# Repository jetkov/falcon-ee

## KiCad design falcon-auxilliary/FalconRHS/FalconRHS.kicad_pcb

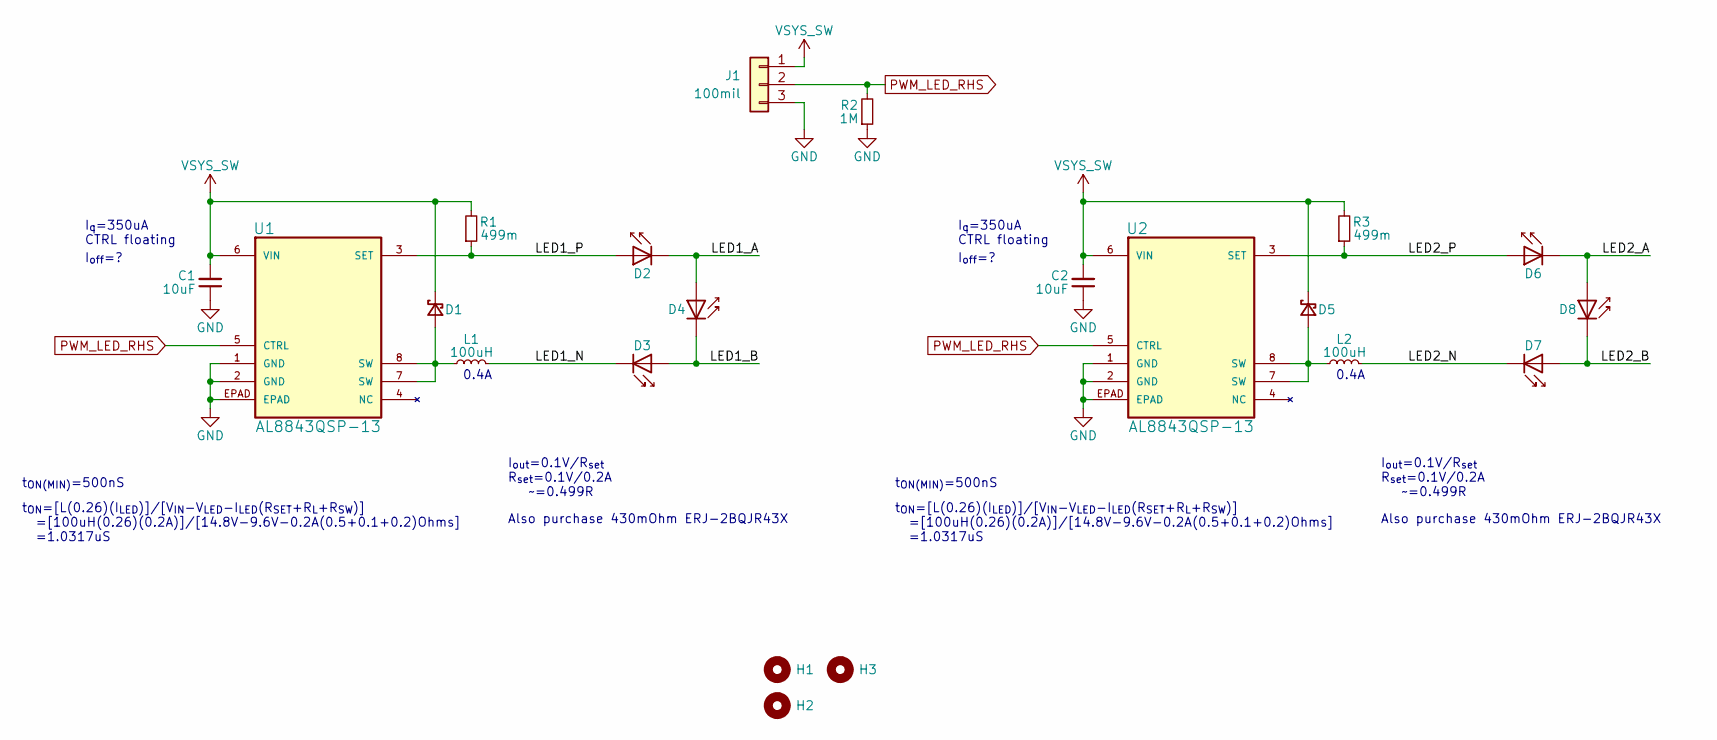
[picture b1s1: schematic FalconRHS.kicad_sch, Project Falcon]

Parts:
C1, C2: 10uF; C_1210_3225Metric; Tolerance 10%; Voltage 50V; Part Number CGA6P3X7S1H106K250AB
D1, D5: 500mA; SC-76-SOD-323_USC_TSB; Part Number CUS551V30,H3F
D2, D3, D4, D6, D7, D8: XQA LED 1616 SMD; XQ-A-LED_Large; Voltage 3.4Vf; Part Number XQAAPA-02-0000-000000Y01
H1, H2, H3: MountingHole; MountingHole_2.7mm_M2.5_Clearanced
J1: 100mil; PinHeader_1x03_P2.54mm_Vertical
L1, L2: 100uH; L_Taiyo-Yuden_NR-60xx_HandSoldering; Tolerance 20%; Part Number NR6028T101M
R1, R3: 499m; R_0402_1005Metric; Tolerance 1%; Part Number RL0402FR-070R499L
R2: 1M; R_0402_1005Metric; Tolerance 1%; Part Number RMCF0402FT1M00
U1, U2: AL8843QSP-13; 8-SOIC_SO-8EP_DIO; Part Number AL8843QSP-13

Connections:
/LED1_A: D2.1 (K), D4.2 (A)
/LED1_B: D3.2 (A), D4.1 (K)
/LED1_N: D3.1 (K), L1.2
/LED1_P: D2.2 (A), R1.1, U1.3 (SET)
/LED2_A: D6.1 (K), D8.2 (A)
/LED2_B: D7.2 (A), D8.1 (K)
/LED2_N: D7.1 (K), L2.2
/LED2_P: D6.2 (A), R3.1, U2.3 (SET)
GND: C1.1, C2.1, J1.3, R2.1, U1.1 (GND), U1.2 (GND), U1.EPAD, U2.1 (GND), U2.2 (GND), U2.EPAD
unnamed: D1.2 (A), L1.1, U1.7 (SW), U1.8 (SW)
unnamed: D5.2 (A), L2.1, U2.7 (SW), U2.8 (SW)
PWM_LED_RHS: J1.2, R2.2, U1.5 (CTRL), U2.5 (CTRL)
VSYS_SW: C1.2, C2.2, D1.1 (K), D5.1 (K), J1.1, R1.2, R3.2, U1.6 (VIN), U2.6 (VIN)

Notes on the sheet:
Also purchase 430mOhm ERJ-2BQJR43X
I_{off}=?
t_{ON(MIN)}=500nS
I_{q}=350uA CTRL floating
t_{ON}=[L(0.26)(I_{LED})]/[V_{IN}-V_{LED}-I_{LED}(R_{SET}+R_{L}+R_{SW})] =[100uH(0.26)(0.2A)]/[14.8V-9.6V-0.2A(0.5+0.1+0.2)Ohms] =1.0317uS
I_{out}=0.1V/R_{set} R_{set}=0.1V/0.2A ~=0.499R
0.4A

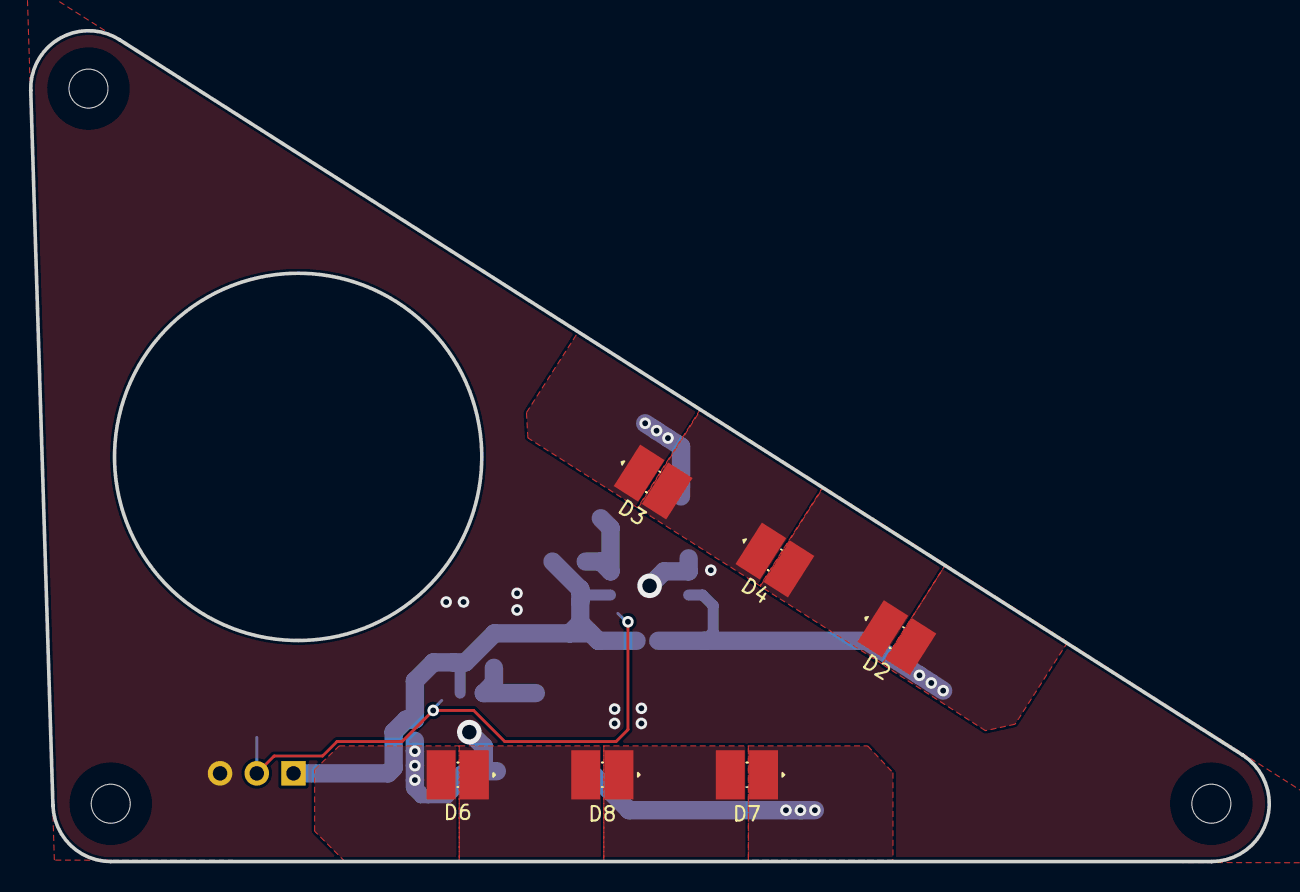
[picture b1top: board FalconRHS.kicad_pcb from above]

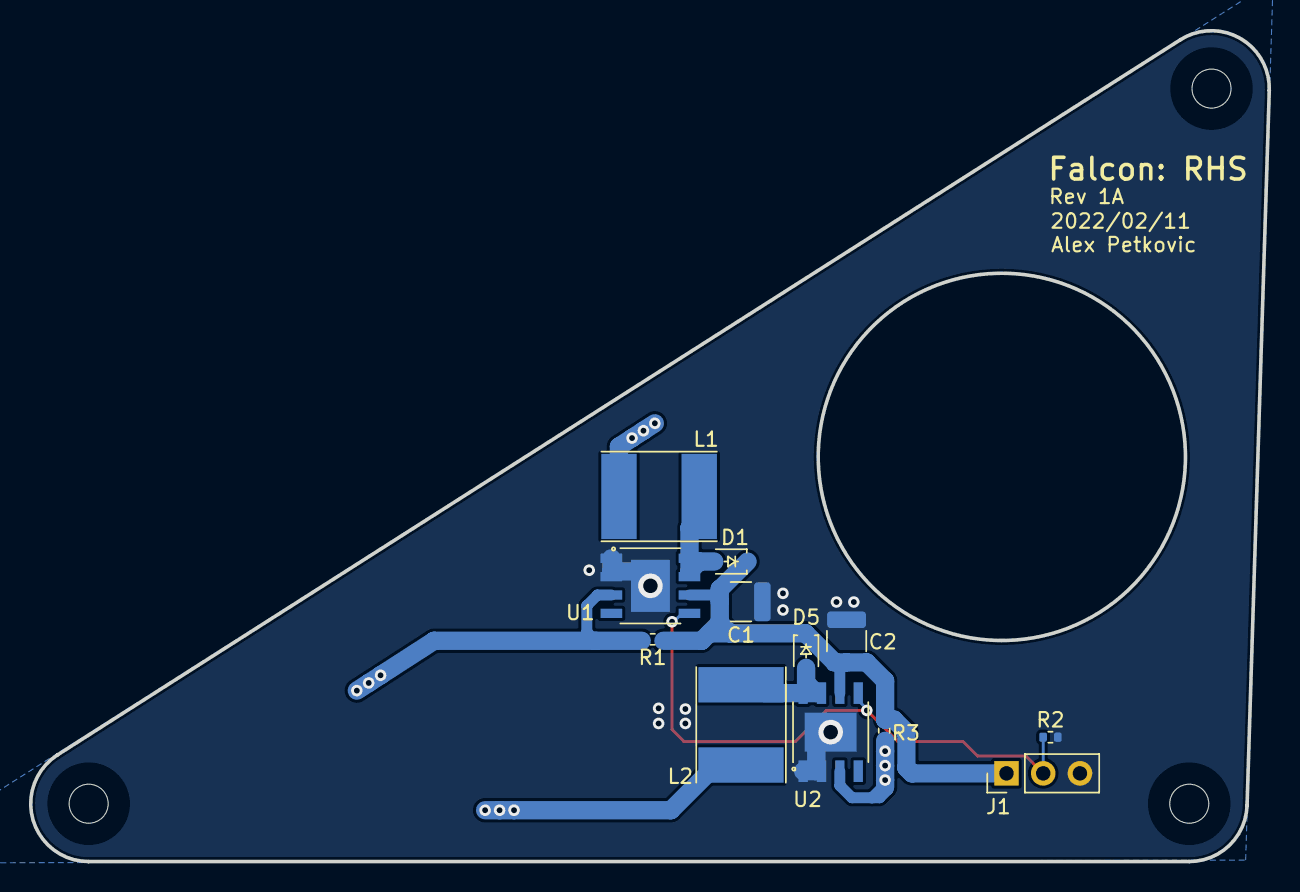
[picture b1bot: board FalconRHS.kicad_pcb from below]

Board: 2 copper layers, 85.7 x 57.5 mm, 21 parts (12 on the bottom side), 13 nets.

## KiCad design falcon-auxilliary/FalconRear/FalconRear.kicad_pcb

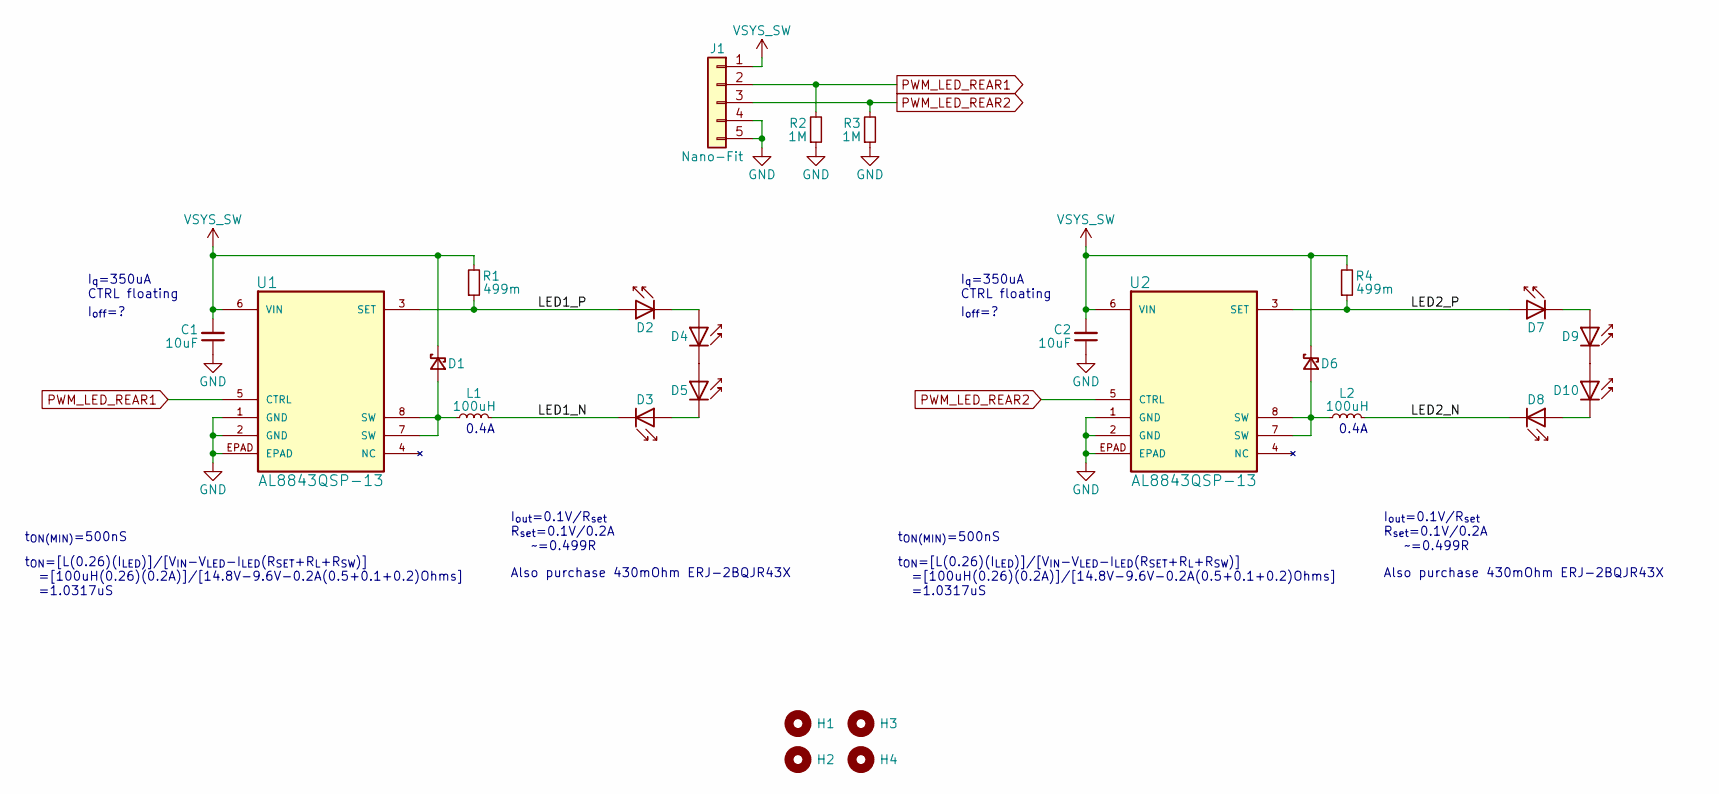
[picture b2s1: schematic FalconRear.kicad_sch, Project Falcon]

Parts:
C1, C2: 10uF; C_1210_3225Metric; Tolerance 10%; Voltage 50V; Part Number CGA6P3X7S1H106K250AB
D1, D6: 500mA; SC-76-SOD-323_USC_TSB; Part Number CUS551V30,H3F
D2, D3, D4, D5, D7, D8, D9, D10: XQA LED 1616 SMD; XQ-A-LED_Large; Voltage 2,2Vf; Part Number XQARED-02-0000-000000W01
H1, H2, H3, H4: MountingHole; MountingHole_2.7mm_M2.5_Clearanced
J1: Nano-Fit; Molex_Nano-Fit_105313-xx05_1x05_P2.50mm_Horizontal; Part Number 1053091105
L1, L2: 100uH; L_Taiyo-Yuden_NR-60xx_HandSoldering; Tolerance 20%; Part Number NR6028T101M
R1, R4: 499m; R_0402_1005Metric; Tolerance 1%; Part Number RL0402FR-070R499L
R2, R3: 1M; R_0402_1005Metric; Tolerance 1%; Part Number RMCF0402FT1M00
U1, U2: AL8843QSP-13; 8-SOIC_SO-8EP_DIO; Part Number AL8843QSP-13

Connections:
/LED1_N: D3.1 (K), L1.2
/LED1_P: D2.2 (A), R1.1, U1.3 (SET)
/LED2_N: D8.1 (K), L2.2
/LED2_P: D7.2 (A), R4.1, U2.3 (SET)
GND: C1.1, C2.1, J1.4, J1.5, R2.1, R3.1, U1.1 (GND), U1.2 (GND), U1.EPAD, U2.1 (GND), U2.2 (GND), U2.EPAD
unnamed: D1.2 (A), L1.1, U1.7 (SW), U1.8 (SW)
unnamed: D2.1 (K), D4.2 (A)
unnamed: D3.2 (A), D5.1 (K)
unnamed: D4.1 (K), D5.2 (A)
unnamed: D6.2 (A), L2.1, U2.7 (SW), U2.8 (SW)
unnamed: D7.1 (K), D9.2 (A)
unnamed: D8.2 (A), D10.1 (K)
unnamed: D9.1 (K), D10.2 (A)
PWM_LED_REAR1: J1.2, R2.2, U1.5 (CTRL)
PWM_LED_REAR2: J1.3, R3.2, U2.5 (CTRL)
VSYS_SW: C1.2, C2.2, D1.1 (K), D6.1 (K), J1.1, R1.2, R4.2, U1.6 (VIN), U2.6 (VIN)

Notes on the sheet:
Also purchase 430mOhm ERJ-2BQJR43X
I_{off}=?
t_{ON(MIN)}=500nS
I_{q}=350uA CTRL floating
t_{ON}=[L(0.26)(I_{LED})]/[V_{IN}-V_{LED}-I_{LED}(R_{SET}+R_{L}+R_{SW})] =[100uH(0.26)(0.2A)]/[14.8V-9.6V-0.2A(0.5+0.1+0.2)Ohms] =1.0317uS
I_{out}=0.1V/R_{set} R_{set}=0.1V/0.2A ~=0.499R
0.4A

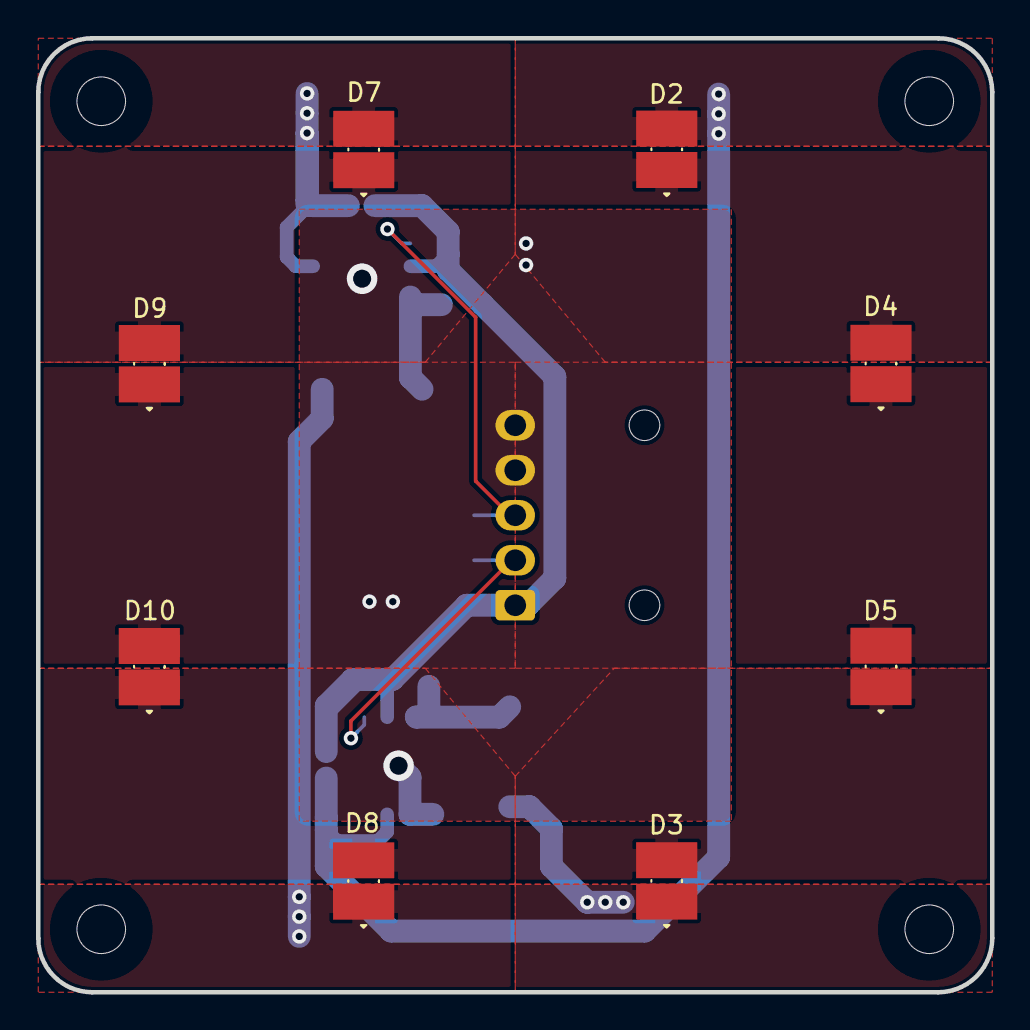
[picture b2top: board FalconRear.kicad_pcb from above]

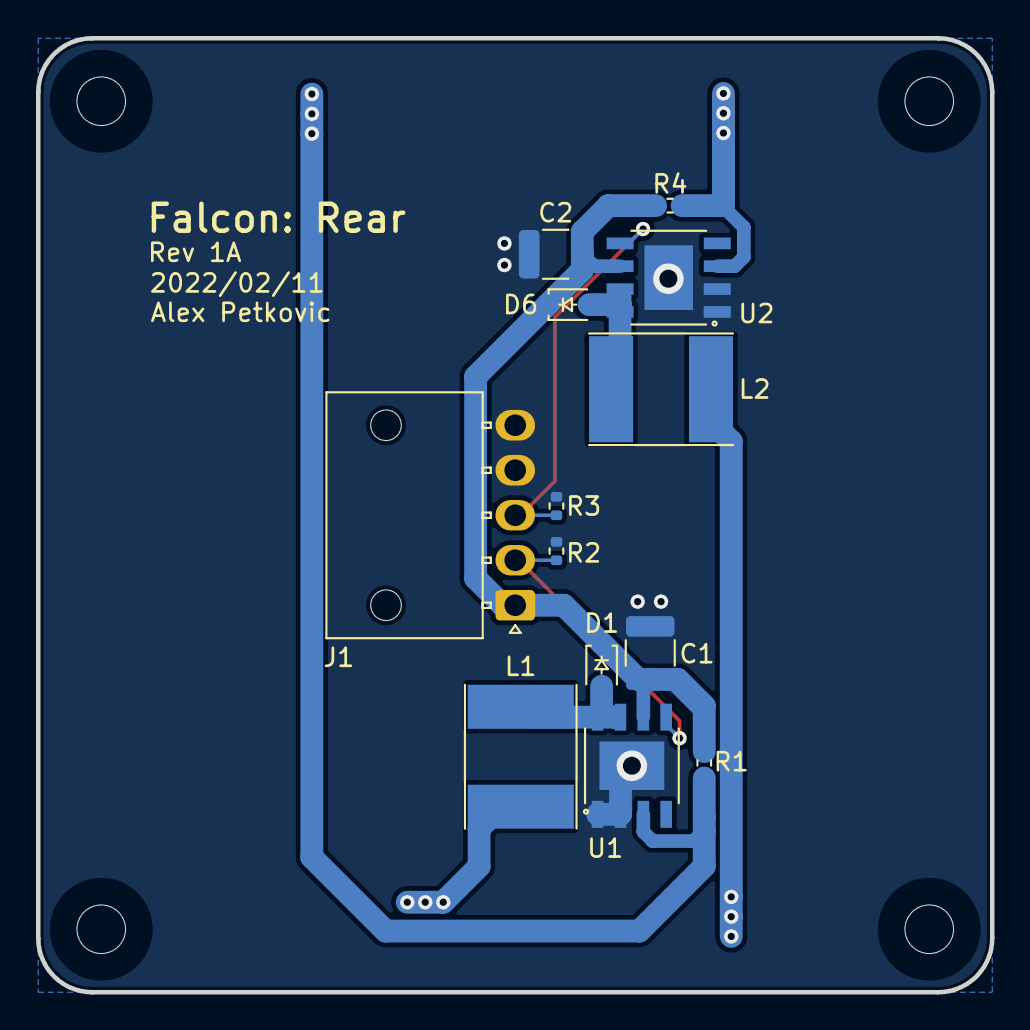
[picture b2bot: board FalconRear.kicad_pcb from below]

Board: 2 copper layers, 53.0 x 53.0 mm, 25 parts (13 on the bottom side), 16 nets.

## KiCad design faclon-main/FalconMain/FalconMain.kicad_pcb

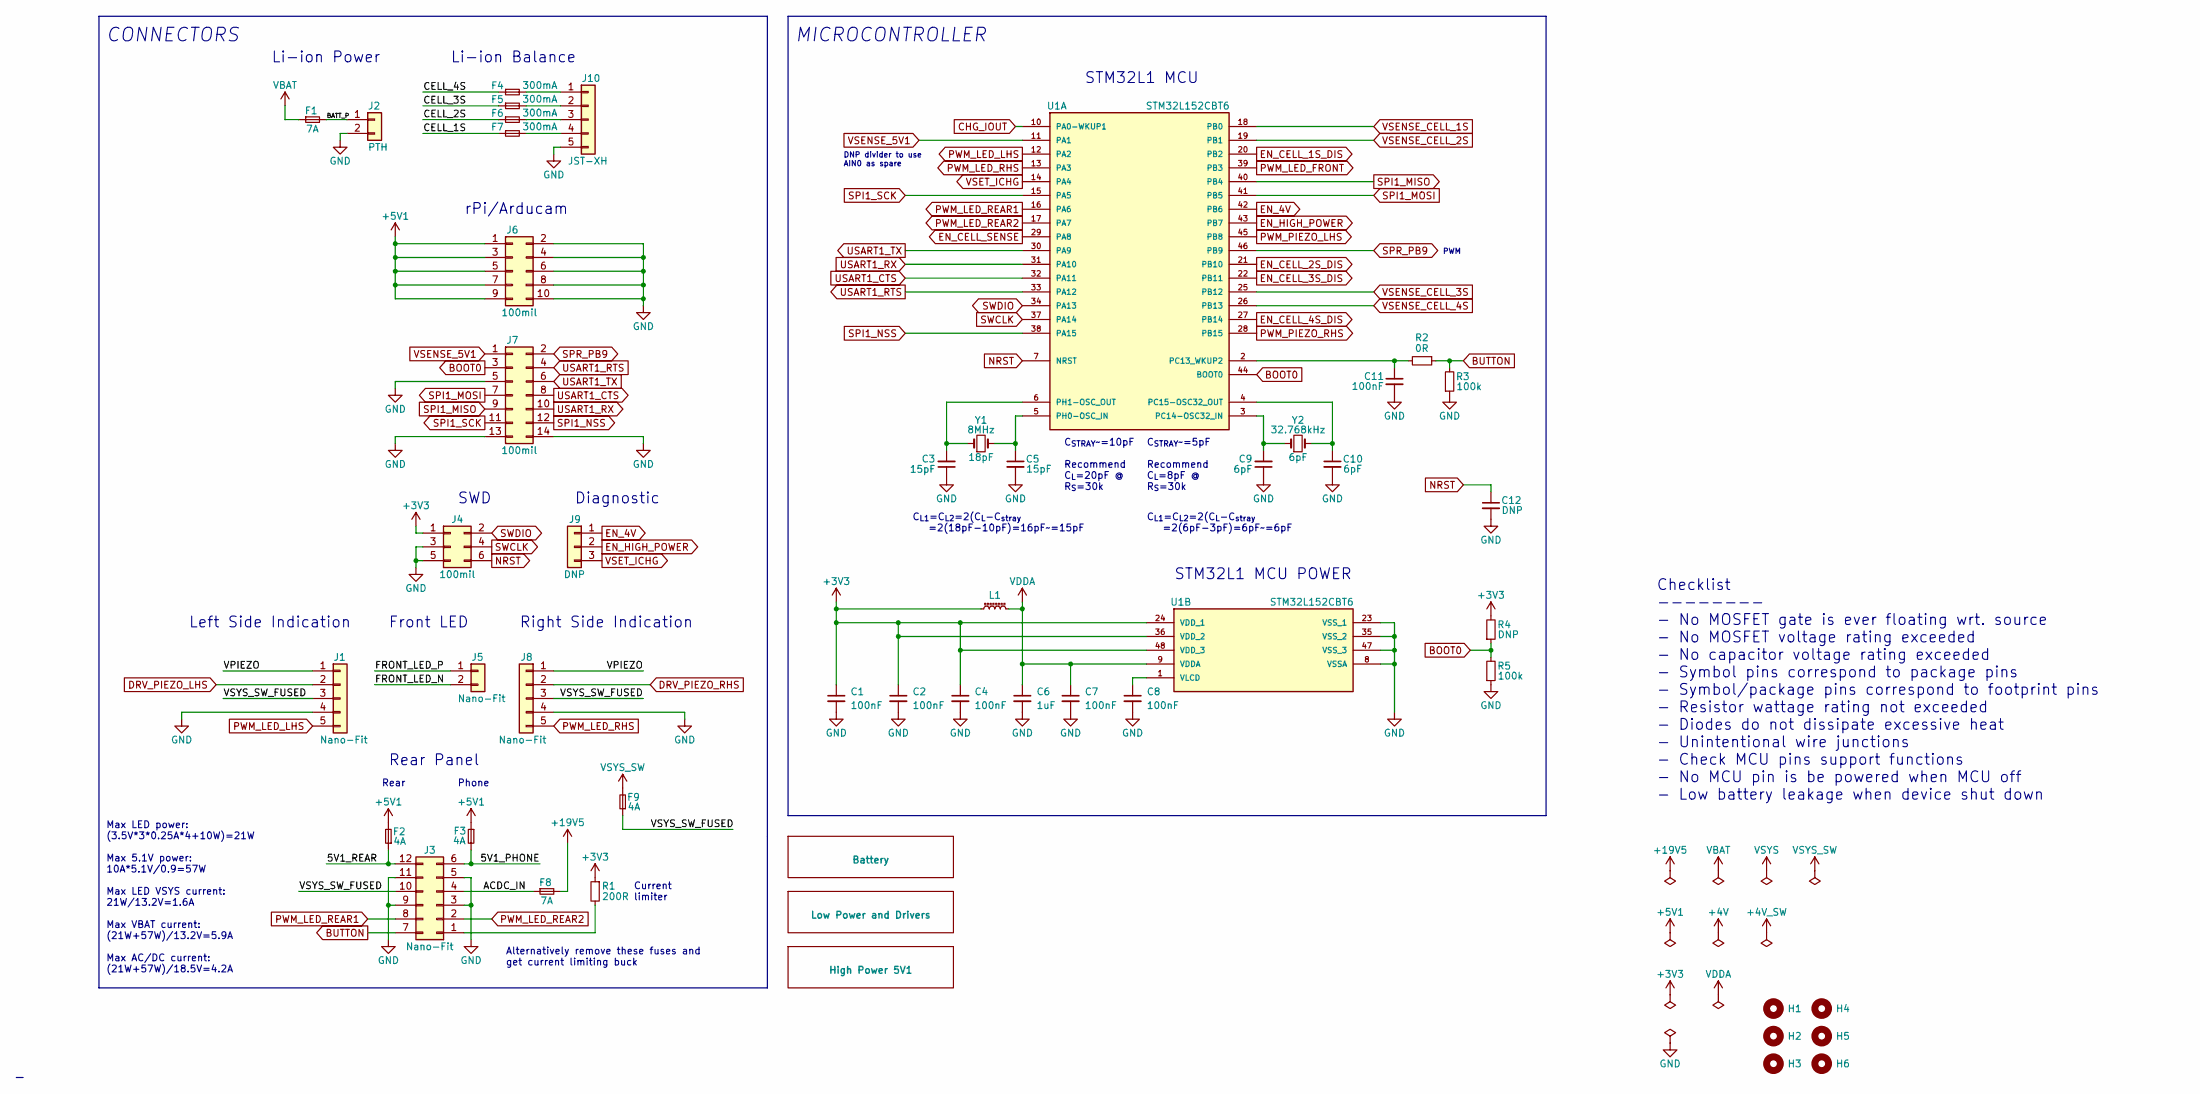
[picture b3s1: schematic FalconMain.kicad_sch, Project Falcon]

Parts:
C1, C2, C4, C7, C8, C11: 100nF; C_0402_1005Metric; Tolerance 10%; Voltage 25V; Part Number GRM155R71E104KE14D
C3, C5: 15pF; C_0402_1005Metric; Tolerance 5%; Voltage 50V; Part Number 885012005056
C6: 1uF; C_0603_1608Metric; Tolerance 10%; Voltage 25V; Part Number CGA3E1X7R1E105K080AC
C9, C10: 6pF; C_0402_1005Metric; Tolerance 0.5pF; Voltage 50V; Part Number CGA2B2C0G1H060D050BA
C12: DNP; C_0402_1005Metric; Tolerance 10%; Voltage 50V; Part Number 885012205061
F1, F8: 7A; R_0603_1608Metric; Voltage 32V; Part Number 0686F7000-01
F2, F3, F9: 4A; R_0402_1005Metric; Voltage 32V; Part Number 3414.0123.26
F4, F5, F6, F7: 300mA; R_0603_1608Metric; Voltage 32V; Part Number C2Q 300
H1, H2, H3, H4, H5, H6: MountingHole; MountingHole_2.7mm_M2.5_Clearanced
J1, J8: Nano-Fit; Molex_Nano-Fit_105309-xx05_1x05_P2.50mm_Vertical; Part Number 1053091105
J2: PTH; Conn_Batt_Wire_10AWG
J3: Nano-Fit; Molex_Nano-Fit_105310-xx12_2x06_P2.50mm_Vertical; Part Number 1053101112
J4: 100mil; PinHeader_2x03_P2.54mm_Vertical; Part Number PREC003DFAN-RC
J5: Nano-Fit; Molex_Nano-Fit_105309-xx02_1x02_P2.50mm_Vertical; Part Number 1053091102
J6: 100mil; PinHeader_2x05_P2.54mm_Vertical
J7: 100mil; PinHeader_2x07_P2.54mm_Vertical
J9: DNP; PinHeader_1x03_P2.54mm_Vertical; Part Number PREC040SAAN-RC
J10: JST-XH; JST_XH_B5B-XH-AM_1x05_P2.50mm_Vertical; Part Number B5B-XH-AM(LF)(SN)
L1: 600 Ohms @ 100 MHz; L_0402_1005Metric; Part Number BLM15AX601SN1D
R1: 200R; R_0603_1608Metric; Tolerance 5%; Part Number RMCF0603JT200R
R2: 0R; R_0402_1005Metric; Tolerance Jumper; Part Number RMCF0402ZT0R00
R3, R5: 100k; R_0402_1005Metric; Tolerance 1%; Part Number RC0402FR-13100KL
R4: DNP; R_0402_1005Metric; Tolerance 1%; Part Number RC0402FR-13100KL
U1: STM32L152CBT6; 48-LQFP_ LQFP48_STM; Part Number STM32L152CBT6
Y1: 8MHz; Crystal_SMD_HC49_WURTH; Tolerance 30ppm; Part Number 830050510
Y2: 32.768kHz; Crystal_DS26_D2.0mm_L6.0mm_Horizontal; Tolerance 20ppm; Part Number 830014219B

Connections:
+3V3: C1.1, C2.1, C4.1, J4.1, L1.1, R1.1, R4.2, U1.24 (VDD_1), U1.36 (VDD_2), U1.48 (VDD_3); also elsewhere on the board
+5V1: F2.2, F3.1, J6.1, J6.3, J6.5, J6.7, J6.9; also elsewhere on the board
+19V5: F8.2; also elsewhere on the board
/5V1_PHONE: F3.2, J3.6
/5V1_REAR: F2.1, J3.12
/ACDC_IN: F8.1, J3.4
/BATT_P: F1.2, J2.1
/CELL_1S: F7.1
/CELL_2S: F6.1
/CELL_3S: F5.1
/CELL_4S: F4.1
/FRONT_LED_N: J5.2
/FRONT_LED_P: J5.1
/VPIEZO: J1.1, J8.1
/VSYS_SW_FUSED: F9.1, J1.3, J3.10, J8.3
BOOT0: J7.3, R4.1, R5.2, U1.44 (BOOT0)
BUTTON: J3.7, R2.1, R3.2
CHG_IOUT: U1.10 (PA0-WKUP1); also elsewhere on the board
DRV_PIEZO_LHS: J1.2; also elsewhere on the board
DRV_PIEZO_RHS: J8.2; also elsewhere on the board
EN_4V: J9.1, U1.42 (PB6); also elsewhere on the board
EN_CELL_1S_DIS: U1.20 (PB2); also elsewhere on the board
EN_CELL_2S_DIS: U1.21 (PB10); also elsewhere on the board
EN_CELL_3S_DIS: U1.22 (PB11); also elsewhere on the board
EN_CELL_4S_DIS: U1.27 (PB14); also elsewhere on the board
EN_CELL_SENSE: U1.29 (PA8); also elsewhere on the board
EN_HIGH_POWER: J9.2, U1.43 (PB7); also elsewhere on the board
GND: C1.2, C2.2, C3.1, C4.2, C5.2, C6.2, C7.2, C8.2, C9.1, C10.2, C11.2, C12.2, J1.4, J2.2, J3.3, J3.5, J3.9, J3.11, J4.3, J4.5, J6.2, J6.4, J6.6, J6.8, J6.10, J7.5, J7.13, J7.14, J8.4, J10.5, R3.1, R5.1, U1.8 (VSSA), U1.23 (VSS_1), U1.35 (VSS_2), U1.47 (VSS_3); also elsewhere on the board
NRST: C12.1, J4.6, U1.7 (NRST)
unnamed: C3.2, U1.6 (PH1-OSC_OUT), Y1.1
unnamed: C5.1, U1.5 (PH0-OSC_IN), Y1.2
unnamed: C8.1, U1.1 (VLCD)
unnamed: C9.2, U1.3 (PC14-OSC32_IN), Y2.1
unnamed: C10.1, U1.4 (PC15-OSC32_OUT), Y2.2
unnamed: C11.1, R2.2, U1.2 (PC13_WKUP2)
unnamed: F4.2, J10.1
unnamed: F5.2, J10.2
unnamed: F6.2, J10.3
unnamed: F7.2, J10.4
unnamed: J3.1, R1.2
PWM_LED_FRONT: U1.39 (PB3); also elsewhere on the board
PWM_LED_LHS: J1.5, U1.12 (PA2)
PWM_LED_REAR1: J3.8, U1.16 (PA6)
PWM_LED_REAR2: J3.2, U1.17 (PA7)
PWM_LED_RHS: J8.5, U1.13 (PA3)
PWM_PIEZO_LHS: U1.45 (PB8); also elsewhere on the board
PWM_PIEZO_RHS: U1.28 (PB15); also elsewhere on the board
SPI1_MISO: J7.9, U1.40 (PB4)
SPI1_MOSI: J7.7, U1.41 (PB5)
SPI1_NSS: J7.12, U1.38 (PA15)
SPI1_SCK: J7.11, U1.15 (PA5)
SPR_PB9: J7.2, U1.46 (PB9)
SWCLK: J4.4, U1.37 (PA14)
SWDIO: J4.2, U1.34 (PA13)
USART1_CTS: J7.8, U1.32 (PA11)
USART1_RTS: J7.4, U1.33 (PA12)
USART1_RX: J7.10, U1.31 (PA10)
USART1_TX: J7.6, U1.30 (PA9)
VBAT: F1.1; also elsewhere on the board
VDDA: C6.1, C7.1, L1.2, U1.9 (VDDA)
VSENSE_5V1: J7.1, U1.11 (PA1); also elsewhere on the board
VSENSE_CELL_1S: U1.18 (PB0); also elsewhere on the board
VSENSE_CELL_2S: U1.19 (PB1); also elsewhere on the board
VSENSE_CELL_3S: U1.25 (PB12); also elsewhere on the board
VSENSE_CELL_4S: U1.26 (PB13); also elsewhere on the board
VSET_ICHG: J9.3, U1.14 (PA4); also elsewhere on the board
VSYS_SW: F9.2; also elsewhere on the board

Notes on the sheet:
Left Side Indication
STM32L1 MCU
rPi/Arducam
Right Side Indication
Current limiter
CONNECTORS
Rear
Rear Panel
Phone
Alternatively remove these fuses and get current limiting buck
PWM
STM32L1 MCU POWER
MICROCONTROLLER
SWD
C_{L1}=C_{L2}=2(C_{L}-C_{stray} =2(18pF-10pF)=16pF~=15pF
Li-ion Power
C_{L1}=C_{L2}=2(C_{L}-C_{stray} =2(6pF-3pF)=6pF~=6pF
DNP divider to use AIN0 as spare
Max LED power: (3.5V*3*0.25A*4+10W)=21W Max 5.1V power: 10A*5.1V/0.9=57W Max LED VSYS current: 21W/13.2V=1.6A Max VBAT current: (21W+57W)/13.2V=5.9A Max AC/DC current: (21W+57W)/18.5V=4.2A
Diagnostic
C_{STRAY}~=5pF Recommend C_{L}=8pF @ R_{S}=30k
Checklist -------- - No MOSFET gate is ever floating wrt. source - No MOSFET voltage rating exceeded - No capacitor voltage rating exceeded - Symbol pins correspond to package pins - Symbol/package pins correspond to footprint pins - Resistor wattage rating not exceeded - Diodes do not dissipate ex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
C_{STRAY}~=10pF Recommend C_{L}=20pF @ R_{S}=30k
Front LED
Li-ion Balance

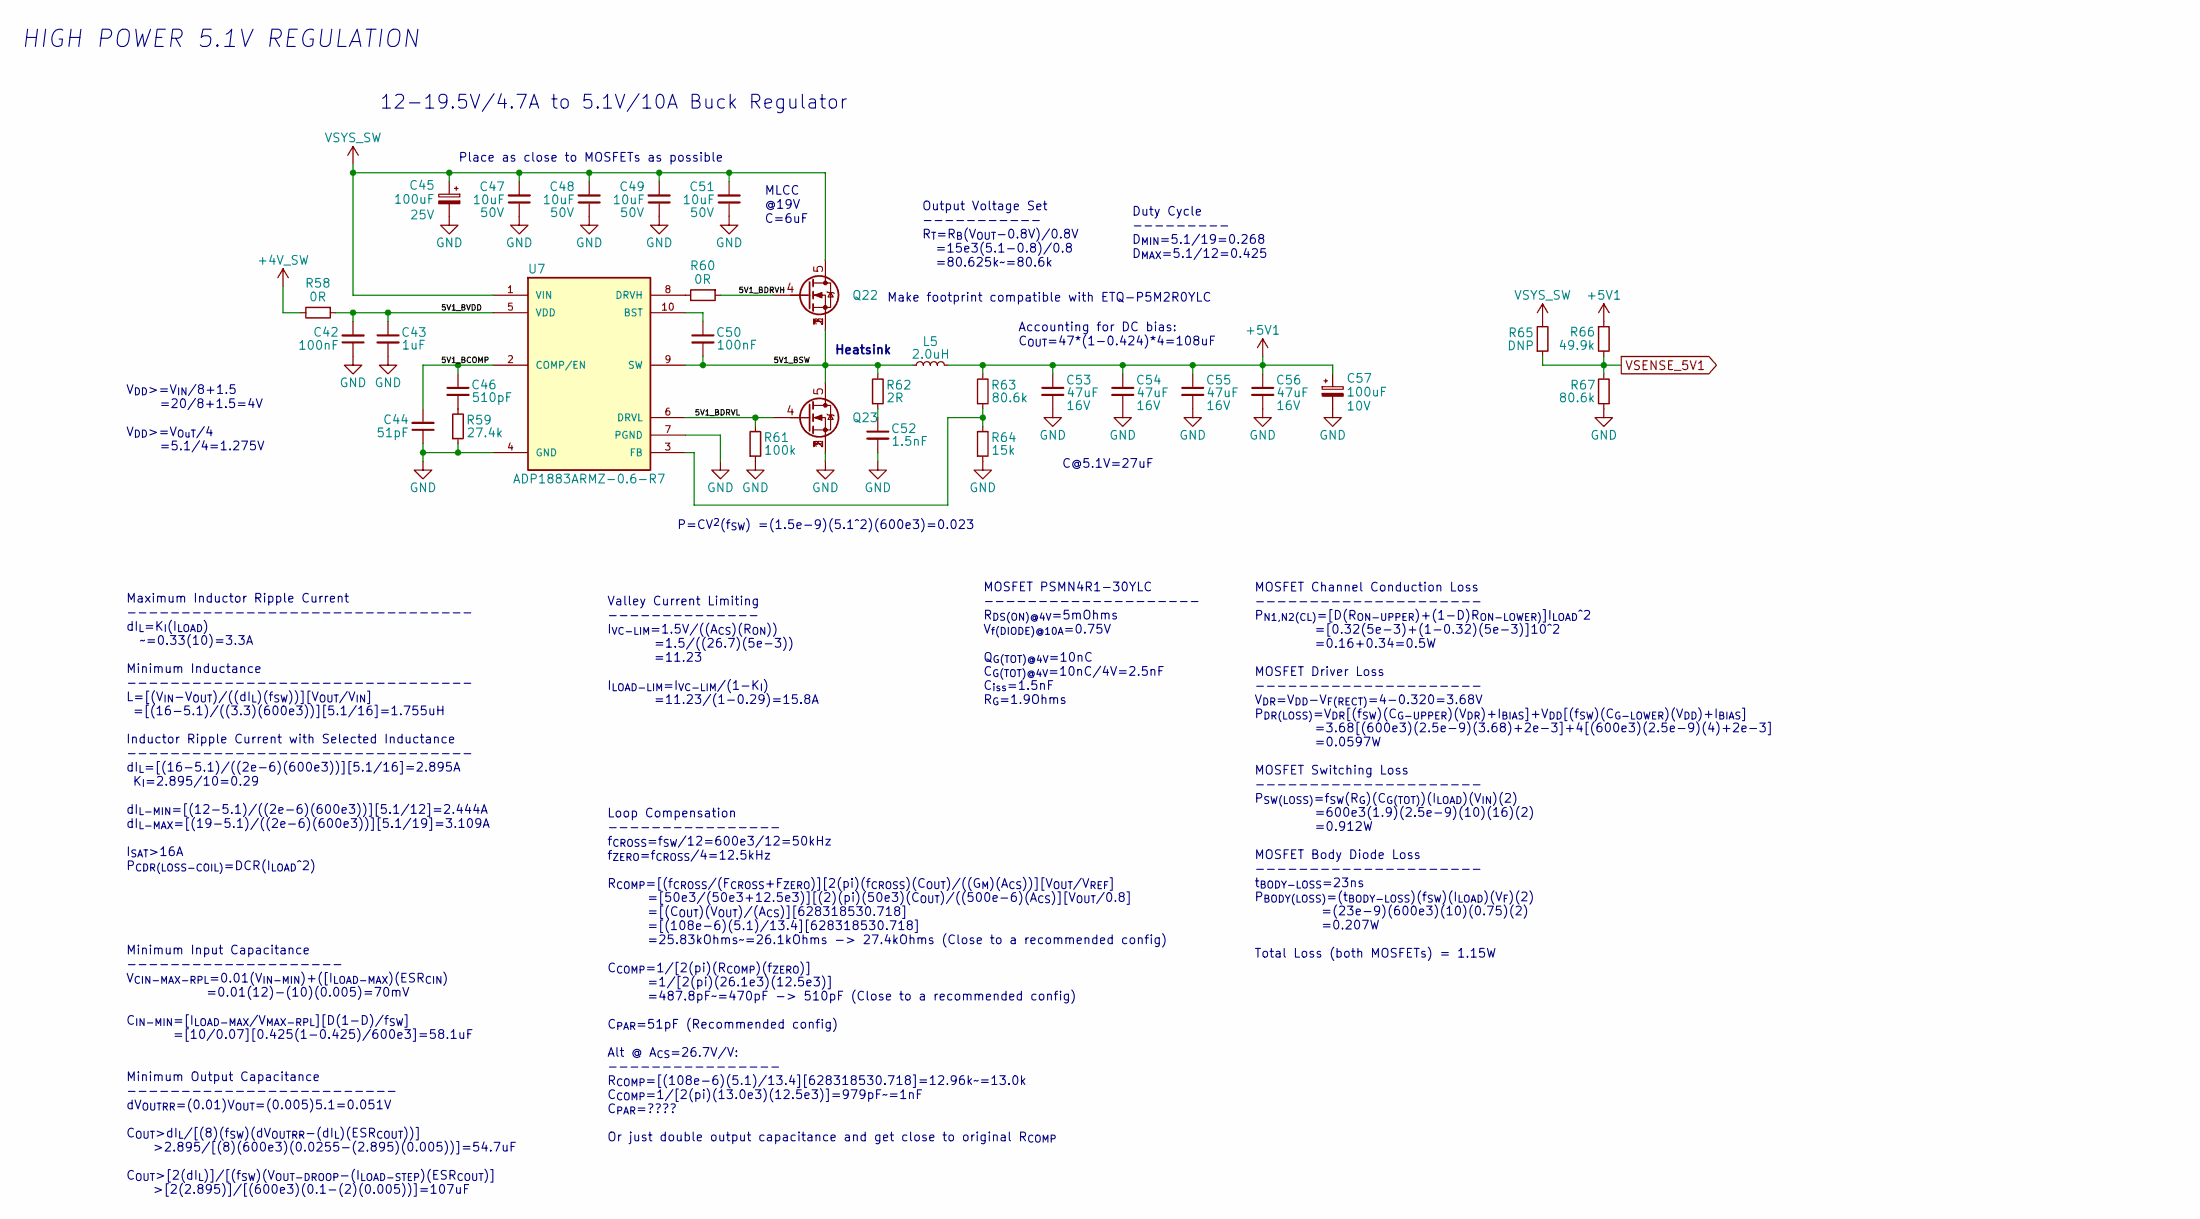
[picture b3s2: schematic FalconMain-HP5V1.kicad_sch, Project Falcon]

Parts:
C42, C50: 100nF; C_0402_1005Metric; Tolerance 10%; Voltage 25V; Part Number GRM155R71E104KE14D
C43: 1uF; C_0603_1608Metric; Tolerance 10%; Voltage 25V; Part Number CGA3E1X7R1E105K080AC
C44: 51pF; C_0402_1005Metric; Tolerance 2%; Voltage 50V; Part Number GRM1555C1H510GA01D
C45: 100uF; CP_Radial_D8.0mm_P3.50mm; Tolerance 20%; Voltage 25V; Part Number A759KS107M1EAAE025
C46: 510pF; C_0402_1005Metric; Tolerance 5%; Voltage 50V; Part Number GRM1555C1H511JA01D
C47, C48, C49, C51: 10uF; C_1210_3225Metric; Tolerance 10%; Voltage 50V; Part Number CGA6P3X7S1H106K250AB
C52: 1.5nF; C_0402_1005Metric; Tolerance 10%; Voltage 25V; Part Number 885012205045
C53, C54, C55, C56: 47uF; C_1210_3225Metric; Tolerance 10%; Voltage 16V; Part Number GRM32EC81C476KE15K
C57: 100uF; CP_Radial_D8.0mm_P3.50mm; Tolerance 20%; Voltage 10V; Part Number RR71A101MDN1
L5: 2.0uH; WE-HCI_1365_7443551; Tolerance 20%; Part Number 7443551200
Q22, Q23: Q_NMOS_LFPAK; LFPACK56-S08_SOT669_NXP; Voltage 20Vgs/30Vds/1.95Vth; Part Number PSMN4R1-30YLC,115
R58, R60: 0R; R_0402_1005Metric; Tolerance Jumper; Part Number RMCF0402ZT0R00
R59: 27.4k; R_0402_1005Metric; Tolerance 1%; Part Number RMCF0402FT27K4
R61: 100k; R_0402_1005Metric; Tolerance 1%; Part Number RC0402FR-13100KL
R62: 2R; R_0402_1005Metric; Tolerance 5%; Part Number RMCF0402JT2R00
R63, R67: 80.6k; R_0402_1005Metric; Tolerance 1%; Part Number RMCF0402FT80K6
R64: 15k; R_0402_1005Metric; Tolerance 1%; Part Number RMCF0402FT15K0
R65: DNP; R_0402_1005Metric; Tolerance 1%; Part Number RMCF0402FT442K
R66: 49.9k; R_0402_1005Metric; Tolerance 1%; Part Number RMCF0402FT49K9
U7: ADP1883ARMZ-0.6-R7; 10-MSOP_RM-10_AD; Part Number ADP1883ARMZ-0.6-R7

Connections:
+4V_SW: R58.2; also elsewhere on the board
+5V1: C53.1, C54.1, C55.1, C56.1, C57.1, L5.2, R63.2, R66.1; also elsewhere on the board
/High Power 5V1/5V1_BCOMP: C44.2, C46.1, U7.2 (COMP/EN)
/High Power 5V1/5V1_BDRVH: Q22.4 (G), R60.1
/High Power 5V1/5V1_BDRVL: Q23.4 (G), R61.2, U7.6 (DRVL)
/High Power 5V1/5V1_BSW: C50.2, L5.1, Q22.1 (S), Q22.2 (S), Q22.3 (S), Q23.5 (D), R62.2, U7.9 (SW)
/High Power 5V1/5V1_BVDD: C42.2, C43.1, R58.1, U7.5 (VDD)
GND: C42.1, C43.2, C44.1, C45.2, C47.1, C48.1, C49.1, C51.1, C52.2, C53.2, C54.2, C55.2, C56.2, C57.2, Q23.1 (S), Q23.2 (S), Q23.3 (S), R59.1, R61.1, R64.1, R67.1, U7.4 (GND), U7.7 (PGND); also elsewhere on the board
unnamed: C46.2, R59.2
unnamed: C50.1, U7.10 (BST)
unnamed: C52.1, R62.1
unnamed: R60.2, U7.8 (DRVH)
unnamed: R63.1, R64.2, U7.3 (FB)
VSENSE_5V1: R65.1, R66.2, R67.2; also elsewhere on the board
VSYS_SW: C45.1, C47.2, C48.2, C49.2, C51.2, Q22.5 (D), R65.2, U7.1 (VIN); also elsewhere on the board

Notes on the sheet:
12-19.5V/4.7A to 5.1V/10A Buck Regulator
P=CV^{2}(f_{SW}) =(1.5e-9)(5.1^2)(600e3)=0.023
Heatsink
Make footprint compatible with ETQ-P5M2R0YLC
HIGH POWER 5.1V REGULATION
V_{DD}>=V_{IN}/8+1.5 =20/8+1.5=4V V_{DD}>=V_{OuT}/4 =5.1/4=1.275V
Accounting for DC bias: C_{OUT}=47*(1-0.424)*4=108uF
Valley Current Limiting -------------- I_{VC-LIM}=1.5V/((A_{CS})(R_{ON})) =1.5/((26.7)(5e-3)) =11.23 I_{LOAD-LIM}=I_{VC-LIM}/(1-K_{I}) =11.23/(1-0.29)=15.8A
Maximum Inductor Ripple Current -------------------------------- dI_{L}=K_{I}(I_{LOAD}) ~=0.33(10)=3.3A Minimum Inductance -------------------------------- L=[(V_{IN}-V_{OUT})/((dI_{L})(f_{SW}))][V_{OUT}/V_{IN}] =[(16-5.1)/((3.3)(600e3))][5.1/16]=1.755uH Inductor Ripple Current with Selected Induct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
C@5.1V=27uF
Place as close to MOSFETs as possible
MOSFET Channel Conduction Loss --------------------- P_{N1,N2(CL)}=[D(R_{ON-UPPER})+(1-D)R_{ON-LOWER)}]I_{LOAD}^2 =[0.32(5e-3)+(1-0.32)(5e-3)]10^2 =0.16+0.34=0.5W MOSFET Driver Loss --------------------- V_{DR}=V_{DD}-V_{F(RECT)}=4-0.320=3.68V P_{DR(LOSS)}=V_{DR}[(f_{SW})(C_{G-UPPER})(V_{DR})+I_{BI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
Loop Compensation ---------------- f_{CROSS}=f_{SW}/12=600e3/12=50kHz f_{ZERO}=f_{CROSS}/4=12.5kHz R_{COMP}=[(f_{CROSS}/(F_{CROSS}+F_{ZERO})][2(pi)(f_{CROSS})(C_{OUT})/((G_{M})(A_{CS}))][V_{OUT}/V_{REF}] =[50e3/(50e3+12.5e3)][(2)(pi)(50e3)(C_{OUT})/((500e-6)(A_{CS})][V_{OUT}/0.8] =[(C_{OUT})(V_{OUT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
Minimum Input Capacitance -------------------- V_{CIN-MAX-RPL}=0.01(V_{IN-MIN})+([I_{LOAD-MAX})(ESR_{CIN}) =0.01(12)-(10)(0.005)=70mV C_{IN-MIN}=[I_{LOAD-MAX}/V_{MAX-RPL}][D(1-D)/f_{SW}] =[10/0.07][0.425(1-0.425)/600e3]=58.1uF Minimum Output Capacitance ------------------------- dV_{OUTRR}=(0.01)V_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
Output Voltage Set ----------- R_{T}=R_{B}(V_{OUT}-0.8V)/0.8V =15e3(5.1-0.8)/0.8 =80.625k~=80.6k
Duty Cycle --------- D_{MIN}=5.1/19=0.268 D_{MAX}=5.1/12=0.425
MOSFET PSMN4R1-30YLC -------------------- R_{DS(ON)@4V}=5mOhms V_{f(DIODE)@10A}=0.75V Q_{G(TOT)@4V}=10nC C_{G(TOT)@4V}=10nC/4V=2.5nF C_{iss}=1.5nF R_{G}=1.9Ohms
MLCC @19V C=6uF
